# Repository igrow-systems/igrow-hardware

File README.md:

# README #

This README would normally document whatever steps are necessary to get your application up and running.

### What is this repository for? ###

* Quick summary
* Version
* [Learn Markdown](https://bitbucket.org/tutorials/markdowndemo)

### Prototype Hardware ###

### How do I get set up? ###

* Summary of set up
* Configuration
* Dependencies
* Database configuration
* How to run tests
* Deployment instructions

### Contribution guidelines ###

* Writing tests
* Code review
* Other guidelines

### Who do I talk to? ###

* Repo owner or admin
* Other community or team contact

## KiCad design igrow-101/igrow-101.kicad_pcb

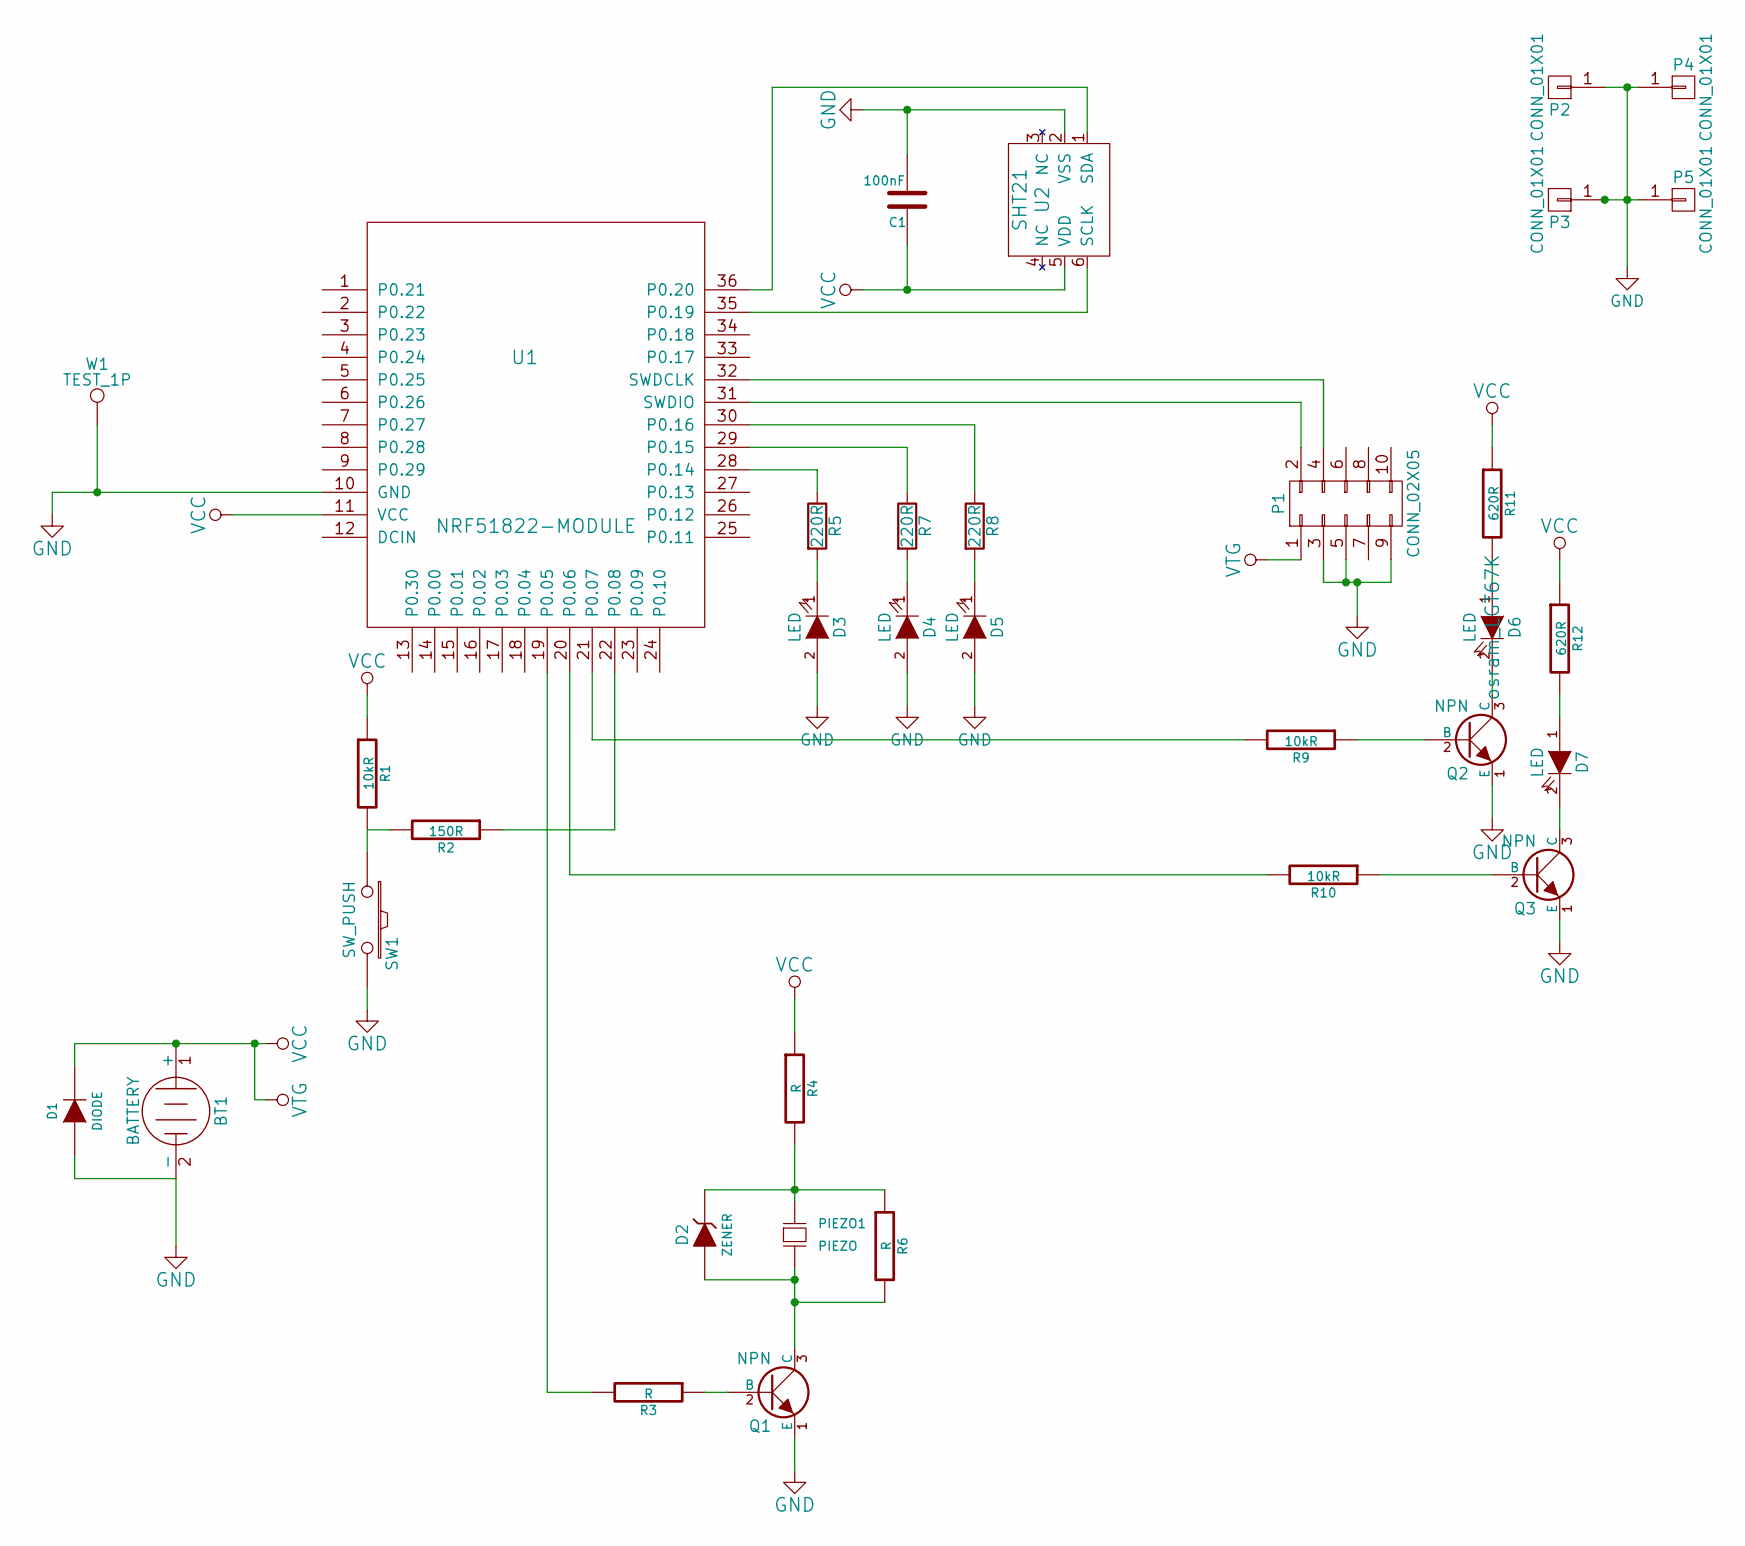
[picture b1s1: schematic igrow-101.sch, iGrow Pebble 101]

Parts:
BT1: BATTERY; CR2032_THRUHOLE
C1: 100nF; C_0603_HandSoldering
D1: DIODE; Diode-SMC_Handsoldering
D2: ZENER; SOD123
D3, D4, D5: LED; LED-5MM
D6, D7: LED; LED_0805
P1: CONN_02X05; harwin_m50-3600542
P2, P3, P4, P5: CONN_01X01; MountingHole_M3
PIEZO1: PIEZO; R_0805_HandSoldering
Q1, Q2, Q3: NPN; SOT-23_Handsoldering_EBC
R1, R9, R10: 10kR; R_0603_HandSoldering
R2: 150R; R_0603_HandSoldering
R3, R4, R6: R; R_0603_HandSoldering
R5, R7, R8: 220R; R_0603_HandSoldering
R11, R12: 620R; R_0603_HandSoldering
SW1: SW_PUSH; SPSTSW
U1: NRF51822-MODULE; XL51822-D01
U2: SHT21; SHT21_HandSoldering
W1: TEST_1P; Measurement_Point_Round-TH_Big

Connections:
GND: BT1.2 (-), C1.2, D1.1 (A), D3.2 (A), D4.2 (A), D5.2 (A), P1.3, P1.5, P1.9, P2.1, P3.1, P4.1, P5.1, Q1.1 (E), Q2.1 (E), Q3.1 (E), SW1.2, U1.10 (GND), U2.2 (VSS), W1.1
unnamed: D2.1 (A), PIEZO1.2, Q1.3 (C), R6.2
unnamed: D2.2 (K), PIEZO1.1, R4.2, R6.1
unnamed: D3.1 (K), R5.2
unnamed: D4.1 (K), R7.2
unnamed: D5.1 (K), R8.2
unnamed: D6.1 (A), R11.2
unnamed: D6.2 (K), Q2.3 (C)
unnamed: D7.1 (A), R12.2
unnamed: D7.2 (K), Q3.3 (C)
unnamed: P1.2, U1.31 (SWDIO)
unnamed: P1.4, U1.32 (SWDCLK)
unnamed: Q1.2 (B), R3.1
unnamed: Q2.2 (B), R9.1
unnamed: Q3.2 (B), R10.1
unnamed: R1.2, R2.2, SW1.1
unnamed: R2.1, U1.22 (P0.08)
unnamed: R3.2, U1.19 (P0.05)
unnamed: R5.1, U1.28 (P0.14)
unnamed: R7.1, U1.29 (P0.15)
unnamed: R8.1, U1.30 (P0.16)
unnamed: R9.2, U1.21 (P0.07)
unnamed: R10.2, U1.20 (P0.06)
unnamed: U1.35 (P0.19), U2.6 (SCLK)
unnamed: U1.36 (P0.20), U2.1 (SDA)
VCC: BT1.1 (+), C1.1, D1.2 (K), P1.1, R1.1, R4.1, R11.1, R12.1, U1.11 (VCC), U2.5 (VDD)

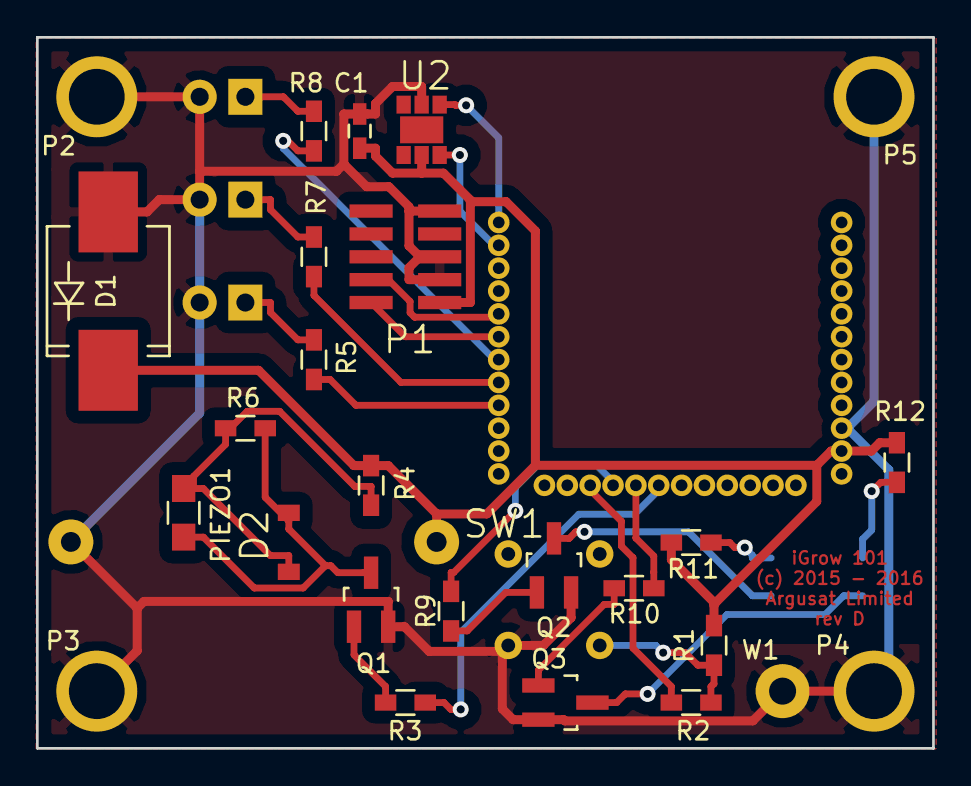
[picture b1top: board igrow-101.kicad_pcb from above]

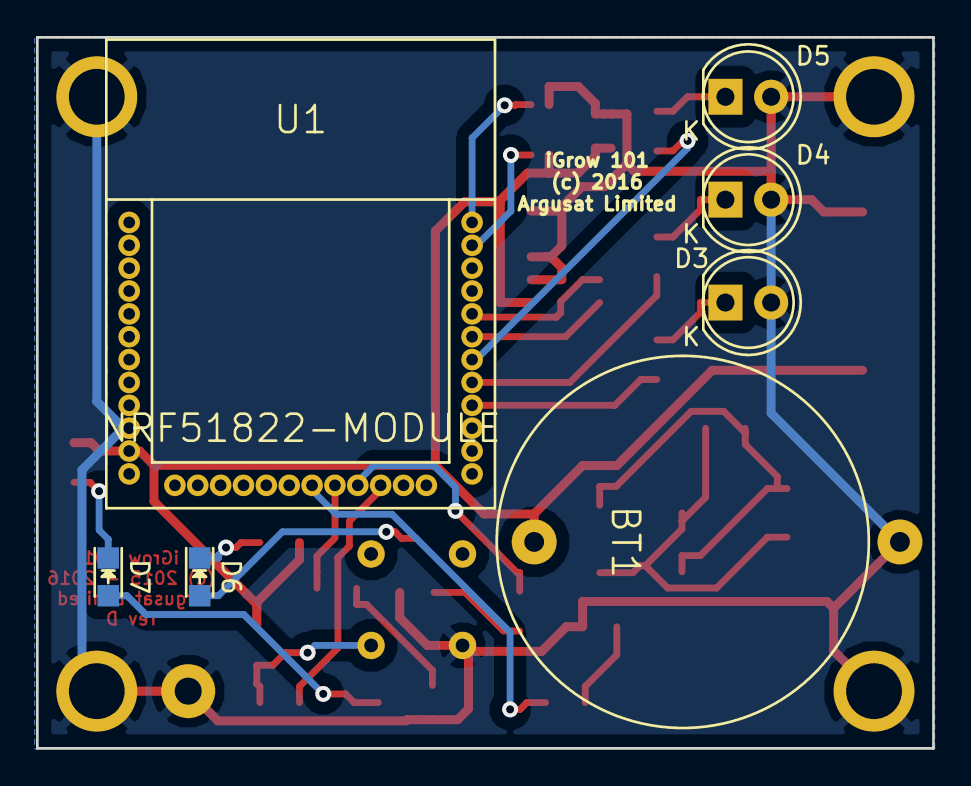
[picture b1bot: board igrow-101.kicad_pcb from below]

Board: 2 copper layers, 49.8 x 39.5 mm, 34 parts (7 on the bottom side), 26 nets.

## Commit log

2015-04-02 Add simulation work and schematic/board WIP
2015-04-06 Post autorouting
2015-04-06 First attempt at cooking a board...
2015-04-11 Flip module to other side, correct header pinout and make the module pads bigger
2015-04-13 Make module copper pads a bit larger
2015-04-13 Rework with 0.381mm minimum track widths
2015-04-13 Rework with 0.508mm/20mil minimum track widths
2015-04-20 Move library dependency local to this repository for now.
2015-04-21 README.md edited online with Bitbucket
2015-11-15 Add photos. Update svgs
2015-11-15 Add PCB 3d render
2016-06-08 First pass at board revision D - use direct connected IR LEDs for sensing
2016-06-09 Revision D as sent to dirtypcbs for fab
2016-06-09 Rename .gm1 -> .gml
2016-07-08 Add simulation updates for osram_LGT67K LED. Not sure why there is a changed polygon in the pcb file...
2016-07-10 Fix diode calibrator script. Add updated LED model. Add calculated schematic values. Add Matlab/octave scripts for plotting simulation output.
2016-08-28 Make nRF51822 module through-holes larger, battery holder through-holes larger. Make pads for SHT21 device larger.
2016-08-28 Correct sizing for module, button cell holder through-holes and enlarge SHT21 pads to allow hand soldering if required.
2016-09-15 Hardware revision F
2016-09-17 Add enclosure script and output for laser cutting.
2017-01-27 Update prototype photo.

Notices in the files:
igrow-101/igrow-101.kicad_pcb:
(c) 2016
(c) 2015 - 2016
